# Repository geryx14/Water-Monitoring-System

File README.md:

# IoT-Based Water Monitoring System

## Description
This project provides an affordable and efficient way to monitor water levels and quality using IoT technology. With real-time data transmission and cloud integration, it ensures better resource management.

## Key Features
- Real-time monitoring of water parameters
- Database integration for remote access
- Simple and scalable design
- to give saveral notifications alert to email and telegram

## Hardware Requirements
- ESP32 microcontroller
- Raspberry pi 4B
- ADS115 Analog Digital Converter
- Ultrasonic sensor (URM-09) : https://wiki.dfrobot.com/URM09_Ultrasonic_Sensor_(Gravity_Analog)_SKU_SEN0307
- Gravity: Analog Turbidity Sensor for Arduino LINK : https://www.dfrobot.com/product-1394.html?srsltid=AfmBOop4nN1BXaXB-rLAD9B4F6cB8y7F4hOIFvNodXXyrF563nFi_e-l
- Gravity: Analog pH Sensor / Meter Pro Kit for Arduino : https://www.dfrobot.com/product-1110.html
- DC PSU 5 Volt
- DC PSU 24 Volt
- Relay 5V DC
- Relay 3 fasa solidstate

## Required Libraries and Dependencies

To ensure the system works properly, install the following libraries and dependencies for ESP32, Raspberry Pi, and Node-RED.

### **ESP32 Libraries**
Ensure the following libraries are installed in the Arduino IDE or PlatformIO:

1. **WiFi Library**  
   - For ESP32 WiFi connectivity.  
   - Built-in with ESP32 core, or install via Board Manager.

2. **PubSubClient**  
   - For MQTT communication.  
   - Install via Arduino Library Manager:  
     ```
     Sketch > Include Library > Manage Libraries > Search for "PubSubClient"
     ```
3. **Ultrasonic sensor (URM-09)** 
   -For HC-SR04 ultrasonic sensor URM-09
   - Install via GitHub:  
     ```
       [[Ultrasonic](https://github.com/JRodrigoTech/Ultrasonic-HC-SR04](https://github.com/DFRobot/DFRobot_URM09))
     
     ```
### **Raspberry Pi Dependencies**
Install the following libraries or packages on your Raspberry Pi:

1. **I2C Communication**  
      first you must to active I2C Communication for raspberry pi
       1. "Sudo Raspi-config"
       2. Interface Options > I2C > Enable
     
4. **MQTT Library**
    Step two you must install MQTT library  
     sudo apt update
     sudo apt upgrade -y
     Sudo pip3 install paho-mqtt

3. **Sensor-Specific Libraries**  
   -For HC-SR04 ultrasonic sensor URM-09
   - Install via GitHub:  
     [[Ultrasonic](https://github.com/JRodrigoTech/Ultrasonic-HC-SR04](https://github.com/DFRobot/DFRobot_URM09))
   -for ADS115 Analog Digital Converter
    - Install via GitHub
      https://github.com/giobauermeister/ads1115-linux-rpi

### **Node-RED Dependencies**
Install the following custom nodes in Node-RED:

1. **Installation Steps:**  
    to use node-red with server for example install node-red in windows comment promt
    - npm install -g --unsafe-perm node-red

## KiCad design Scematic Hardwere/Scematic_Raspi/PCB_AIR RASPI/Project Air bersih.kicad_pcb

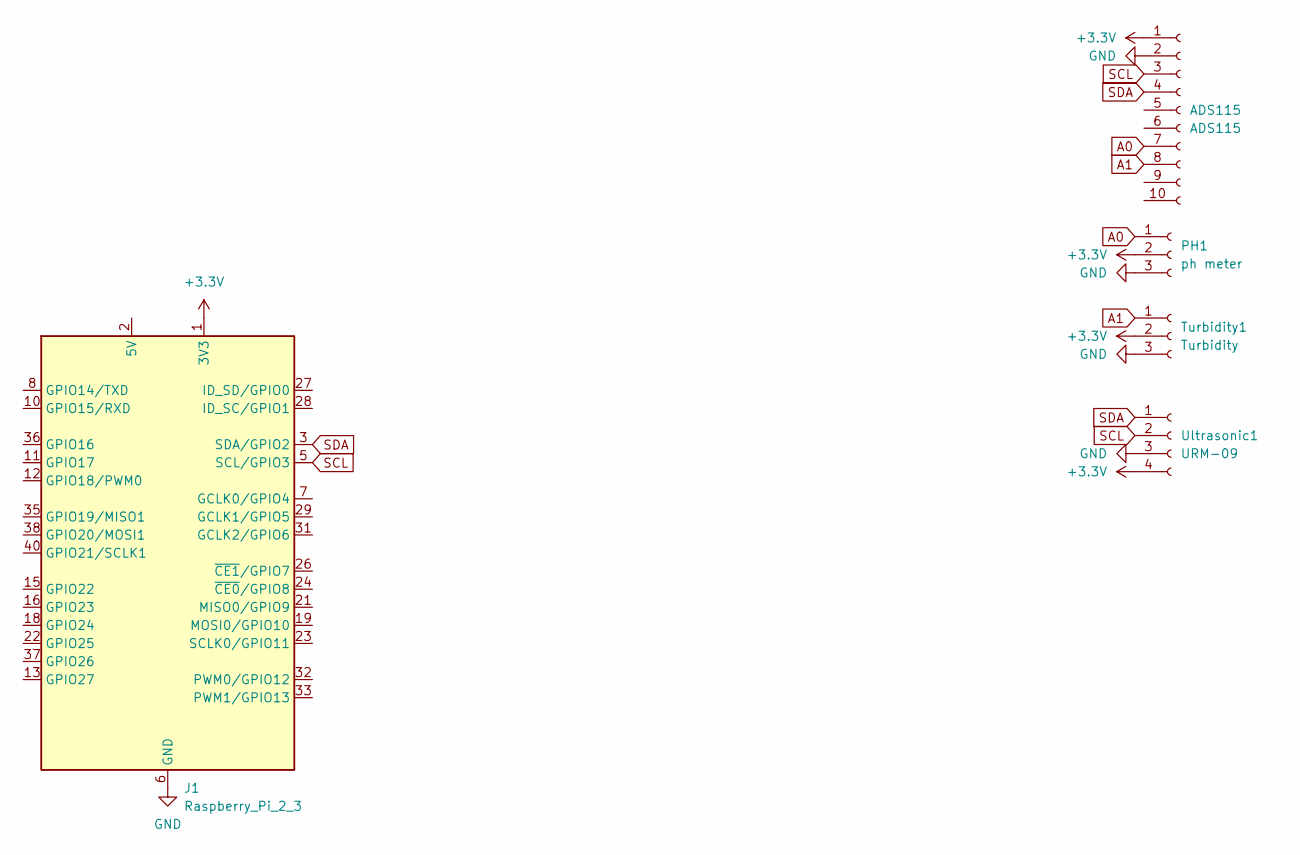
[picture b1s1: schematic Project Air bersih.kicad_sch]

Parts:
ADS115: ADS115; Hirose_DF13-10P-1.25DSA_1x10_P1.25mm_Vertical
J1: Raspberry_Pi_2_3; PinHeader_2x20_P2.54mm_Vertical
PH1: ph meter; JST_EH_B3B-EH-A_1x03_P2.50mm_Vertical
Turbidity1: Turbidity; JST_EH_B3B-EH-A_1x03_P2.50mm_Vertical
Ultrasonic1: URM-09; JST_EH_B4B-EH-A_1x04_P2.50mm_Vertical

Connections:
+3.3V: ADS115.1, J1.1 (3V3), J1.17 (3V3), PH1.2, Turbidity1.2, Ultrasonic1.4
A0: ADS115.7, PH1.1
A1: ADS115.8, Turbidity1.1
GND: ADS115.2, J1.6 (GND), J1.9 (GND), J1.14 (GND), J1.20 (GND), J1.25 (GND), J1.30 (GND), J1.34 (GND), J1.39 (GND), PH1.3, Turbidity1.3, Ultrasonic1.3
unnamed: J1.2 (5V), J1.4 (5V)
SCL: ADS115.3, J1.5 (SCL/GPIO3), Ultrasonic1.2
SDA: ADS115.4, J1.3 (SDA/GPIO2), Ultrasonic1.1

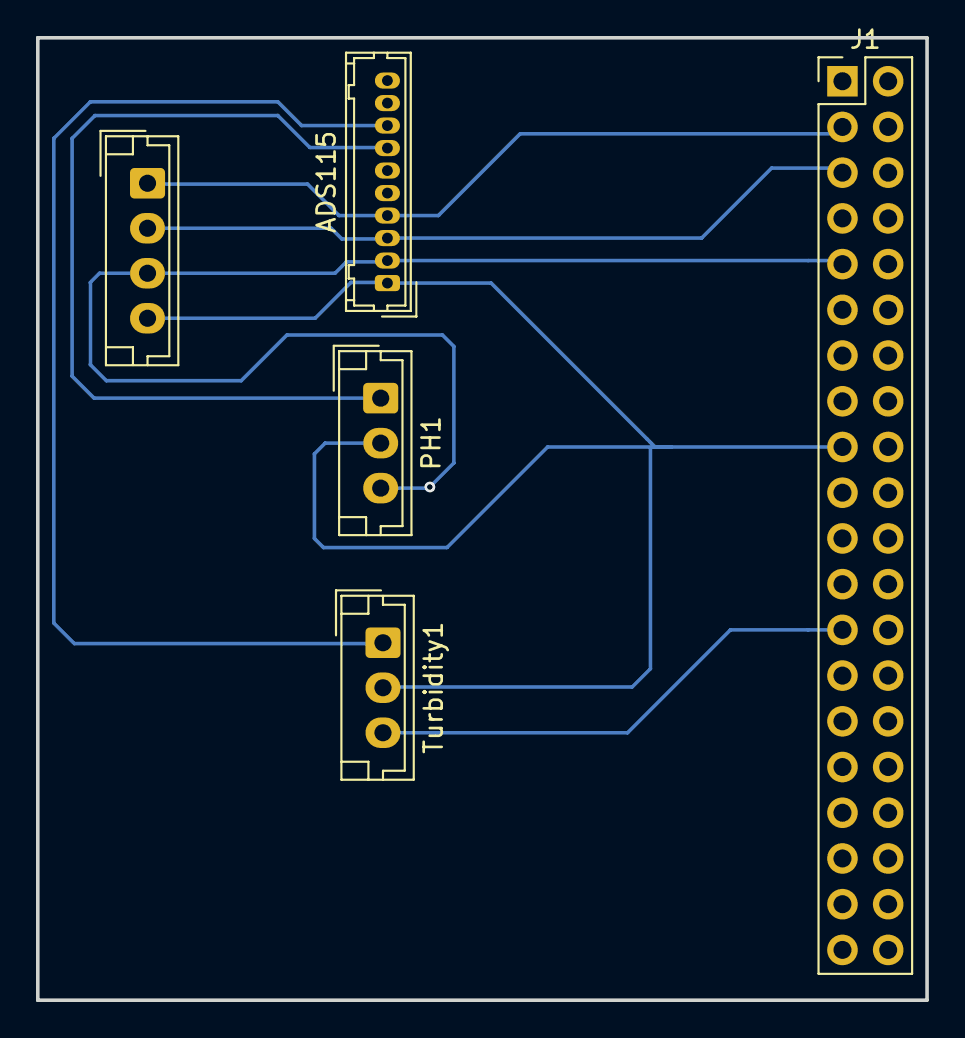
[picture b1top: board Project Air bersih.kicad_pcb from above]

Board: 2 copper layers, 49.4 x 53.5 mm, 5 parts (0 on the bottom side), 7 nets.

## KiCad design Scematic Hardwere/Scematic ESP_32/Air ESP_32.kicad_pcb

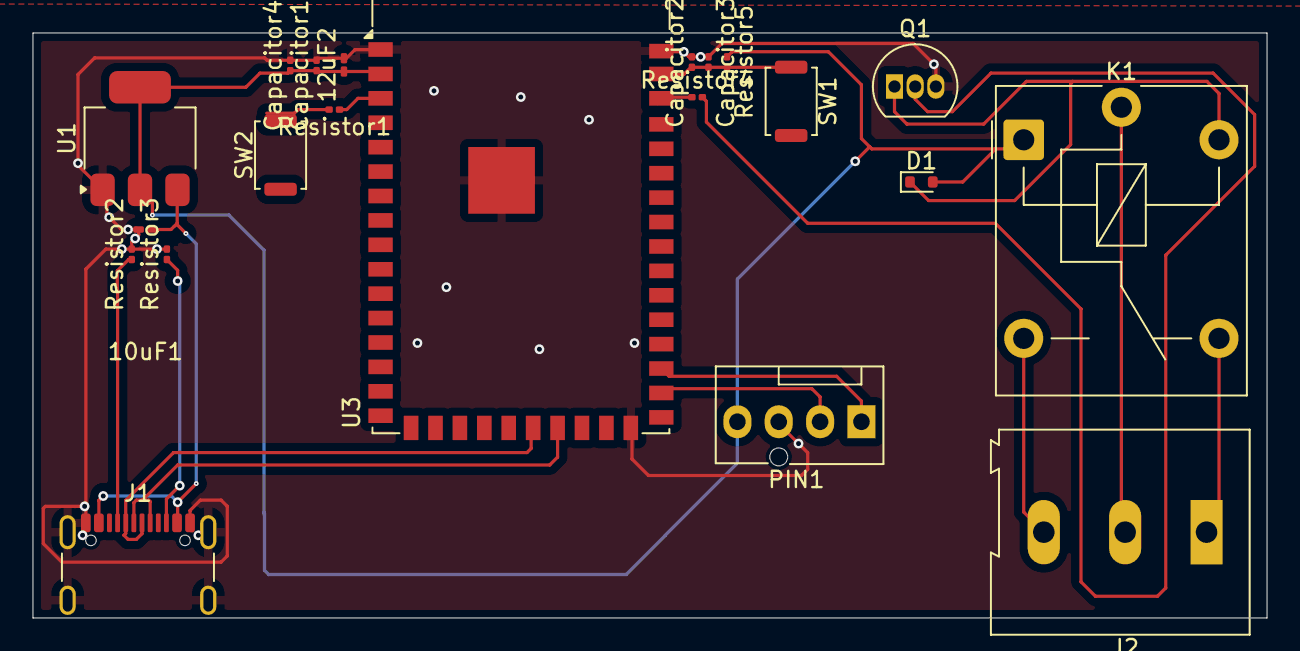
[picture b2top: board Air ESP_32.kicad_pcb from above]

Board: 2 copper layers, 75.8 x 35.9 mm, 21 parts (0 on the bottom side), 18 nets.

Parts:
10uF1, 12uF2: c; C_0201_0603Metric_Pad0.64x0.40mm_HandSolder
Capacitor1: 10nf; C_0201_0603Metric
Capacitor2, Capacitor3: 1uF; C_0201_0603Metric
Capacitor4: 22uf; C_0201_0603Metric
D1: 1N4148WT; D_SOD-523
J1: USB_C_Receptacle_USB2.0_16P; USB_C_Receptacle_GCT_USB4105-xx-A_16P_TopMnt_Horizontal
J2: Screw_Terminal_01x03; TerminalBlock_Altech_AK300-3_P5.00mm
K1: FINDER-36.11; Relay_SPDT_Finder_36.11
PIN1: Ultrasonic URM-09; FanPinHeader_1x04_P2.54mm_Vertical
Q1: BC547; TO-92_Inline
Resistor1, Resistor4: 100R; R_0201_0603Metric
Resistor2, Resistor3, Resistor5: 10k; R_0201_0603Metric
SW1, SW2: SW_MEC_5G; SW_Push_SPST_NO_Alps_SKRK
U1: AMS1117; SOT-223-3_TabPin2
U3: ESP32-S2-WROVER

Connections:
+3.3V: 12uF2.1, Capacitor1.1, Capacitor4.1, D1.2 (A), K1.A1, PIN1.4, Resistor5.1, U1.2 (VO), U3.2 (3V3)
+5V: 10uF1.1, J1.A4 (VBUS), J1.A9 (VBUS), J1.B4 (VBUS), J1.B9 (VBUS), U1.3 (VI)
BOOT: Resistor1.1, U3.3 (IO00)
D+: J1.A6 (D+), J1.B6 (D+), U3.23 (USB_D+)
D-: J1.A7 (D-), J1.B7 (D-), U3.22 (USB_D-)
EN: Capacitor2.1, Capacitor3.2, Resistor5.2, SW1.1 (A), SW1.2 (A), U3.41 (EN)
GND: 10uF1.2, 12uF2.2, Capacitor1.2, Capacitor2.2, Capacitor3.1, Capacitor4.2, J1.A1 (GND), J1.A12 (GND), J1.B1 (GND), J1.B12 (GND), J1.S1 (SHIELD), PIN1.3, Q1.3 (E), Resistor2.2, Resistor3.2, U1.1 (ADJ), U3.1 (GND), U3.26 (GND), U3.42 (GND), U3.43 (GND)
unnamed: D1.1 (K), K1.A2, Q1.1 (C)
unnamed: J1.A5 (CC1), Resistor2.1
unnamed: J1.B5 (CC2), Resistor3.1
unnamed: J2.1, K1.12
unnamed: J2.2, K1.11
unnamed: J2.3, K1.14
unnamed: Q1.2 (B), Resistor4.2
unnamed: Resistor1.2, SW2.1 (A), SW2.2 (A)
R: Resistor4.1, U3.40 (IO46)
SCL: PIN1.2, U3.28 (IO34)
SDA: PIN1.1, U3.29 (IO35)

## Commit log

2025-01-06 README.md
